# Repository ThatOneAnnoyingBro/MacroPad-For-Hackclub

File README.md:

# MacroPad-For-Hackclub
This is my first ever macropad made to be submitted to hackclub

So this is quite a simple pad, nothing too fancy...

#SCHEMATIC

Simple, also still im new to this so uhh....sorry for the bad design 😂😂

#PCB

Case tohhh...i dont have a proper screenshot yet, but it shall be made once recieved

firmware based, they are all made via https://qmk.fm/ here. And i also used VIA so i can easily change the settings of the keys. Right now its set as:

SW1 → Play/Pause, SW2 → Mute, SW3 → Vol Down, SW4 → Vol Up, SW5 → Stop
Encoder 1 → Volume up/down when rotating
Encoder 2 → Scroll up/down when rotating

But it shall be changed later...

# BOM: 
* Seeed XIAO RP2040 (U1)
* Rotary Encoders x2 (SW9, SW10) — Alps EC11E footprint
* Tactile switches x5 (SW1-SW5)
* 0.91" OLED display (I2C, SSD1306, 128x32)
* 3D printed case x1

  Welp thats it. thanks again to yall!!!

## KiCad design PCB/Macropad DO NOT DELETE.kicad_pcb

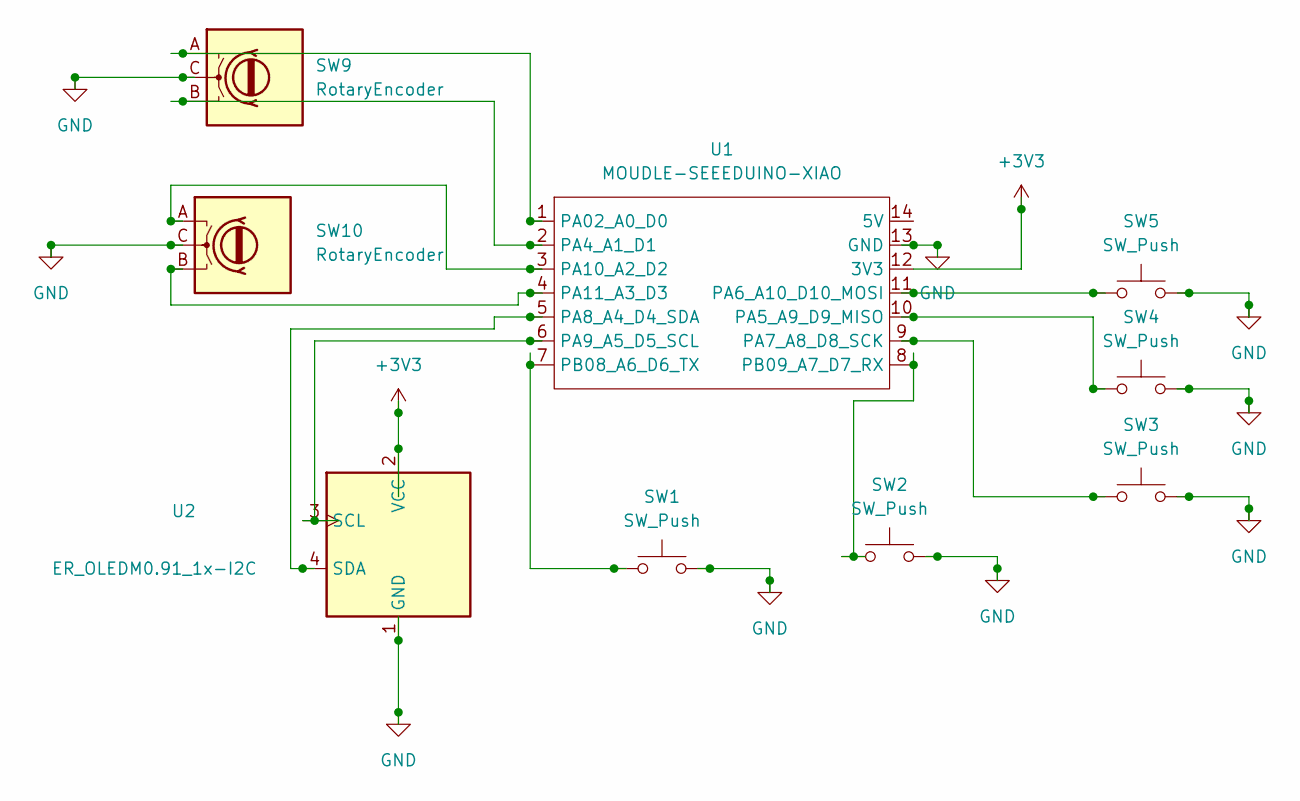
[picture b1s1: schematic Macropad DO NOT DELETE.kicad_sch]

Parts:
SW1, SW2, SW3, SW4, SW5: SW_Push; SW_Cherry_MX_1.00u_PCB
SW9, SW10: RotaryEncoder; RotaryEncoder_Alps_EC11E-Switch_Vertical_H20mm
U1: MOUDLE-SEEEDUINO-XIAO; XIAO-Generic-Hybrid-14P-2.54-21X17.8MM
U2: ER_OLEDM0.91_1x-I2C

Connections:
+3V3: U1.12 (3V3), U2.2 (VCC)
GND: SW1.2, SW2.2, SW3.2, SW4.2, SW5.2, SW9.C, SW10.C, U1.13 (GND), U2.1 (GND)
unnamed: SW9.A, U1.1 (PA02_A0_D0)
unnamed: SW9.B, U1.2 (PA4_A1_D1)
unnamed: SW4.1, U1.10 (PA5_A9_D9_MISO)
unnamed: SW5.1, U1.11 (PA6_A10_D10_MOSI)
unnamed: SW3.1, U1.9 (PA7_A8_D8_SCK)
unnamed: U1.5 (PA8_A4_D4_SDA), U2.4 (SDA)
unnamed: U1.6 (PA9_A5_D5_SCL), U2.3 (SCL)
unnamed: SW10.A, U1.3 (PA10_A2_D2)
unnamed: SW10.B, U1.4 (PA11_A3_D3)
unnamed: SW1.1, U1.7 (PB08_A6_D6_TX)
unnamed: SW2.1, U1.8 (PB09_A7_D7_RX)

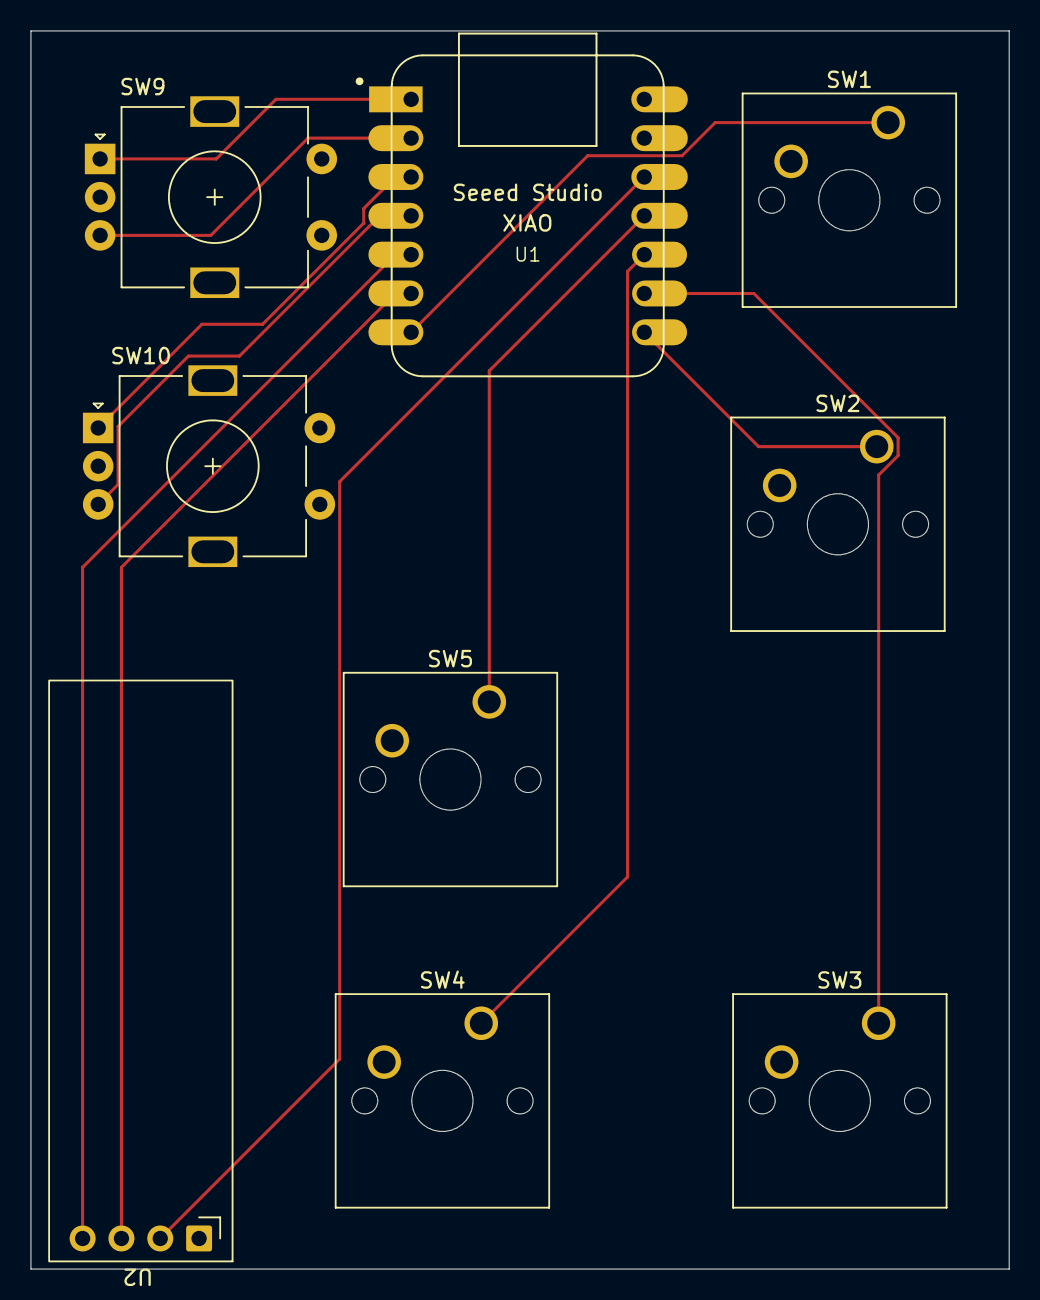
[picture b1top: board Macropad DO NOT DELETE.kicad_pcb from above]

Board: 2 copper layers, 64.0 x 81.0 mm, 9 parts (0 on the bottom side), 13 nets.

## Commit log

2026-03-30 Expand README with project details
    Added detailed project information, including CAD screenshots, schematic, PCB design, firmware details, and bill of materials (BOM).
2026-03-30 Final commit
2026-03-30 Revise README for clarity and conciseness
    Updated the README to simplify language and improve clarity.
2026-03-31 after rechecking
2026-04-07 Update README with new PCB image and design notes
    Removed duplicate design comments and added a new PCB image.
